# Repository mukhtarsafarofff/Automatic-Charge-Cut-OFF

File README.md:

(ENG)   It continuously detects battery charging voltage and once the battery reaches the full charge level, cuts off the charging voltage.

(DEU)   Es erkennt die Ladespannung des Akkus und sobald der Akku den vollen Ladezustand erreicht hat, wird die Ladespannung abgeschaltet.

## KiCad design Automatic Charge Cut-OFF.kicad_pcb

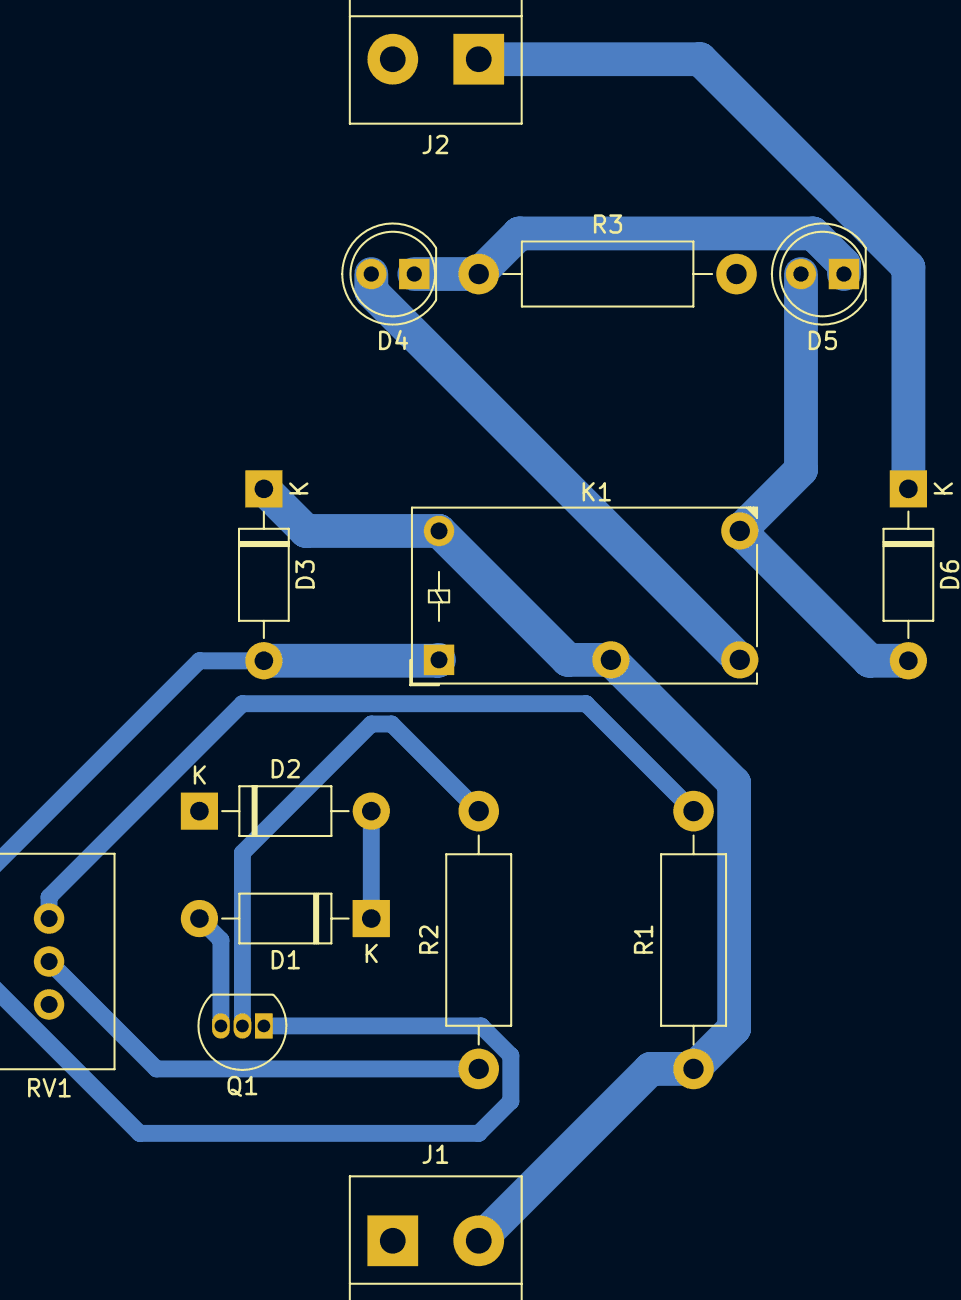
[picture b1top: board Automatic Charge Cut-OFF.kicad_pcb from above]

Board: 2 copper layers, 14 parts (0 on the bottom side), 12 nets.

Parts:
D1, D2, D3, D6: 1N4007; D_DO-41_SOD81_P10.16mm_Horizontal
D4: White; LED_D5.0mm_Clear
D5: Red; LED_D5.0mm
J1: 14,4V; TerminalBlock_bornier-2_P5.08mm
J2: Accumulator; TerminalBlock_bornier-2_P5.08mm
K1: FINDER-32.21-x000; Relay_SPDT_Finder_32.21-x000
Q1: BC547; TO-92_Inline
R1: 10K; R_Axial_DIN0411_L9.9mm_D3.6mm_P15.24mm_Horizontal
R2: 100R; R_Axial_DIN0411_L9.9mm_D3.6mm_P15.24mm_Horizontal
R3: 470R; R_Axial_DIN0411_L9.9mm_D3.6mm_P15.24mm_Horizontal
RV1: 100K; Potentiometer_Vishay_148-149_Single_Horizontal

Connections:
Collector: D3.2 (A), K1.A1, Q1.1 (C)
Earth: D2.1 (K), J1.1, J2.2, R3.2, RV1.3
unnamed: D1.2 (A), Q1.3 (E)
unnamed: D1.1 (K), D2.2 (A)
unnamed: D4.2 (A), K1.14
unnamed: D4.1 (K), D5.1 (K), R3.1
unnamed: D5.2 (A), D6.2 (A), K1.12
unnamed: D6.1 (K), J2.1
unnamed: Q1.2 (B), R2.2
unnamed: R1.2, RV1.1
unnamed: R2.1, RV1.2
VCC: D3.1 (K), J1.2, K1.11, K1.A2, R1.1

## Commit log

2024-03-19 Automatic charge cut off is accomplished
2024-03-25 Automatic charge cut off is renewed
